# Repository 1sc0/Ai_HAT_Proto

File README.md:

## Ai\_HAT\_Proto

PCB design files (EAGLE) for a Raspberry Pi A+/B+/2/3 HAT with a
perma/proto-board section for soldering components. Features 3-Pin and 4-Pin JST
connectors.

## Description

Visit our online shop at:

   * https://acrobotic.com/

Designed by ACROBOTIC Industries.  Please consider buying products from us to 
help fund future Open-Source projects like this! We’ll always put our best 
effort in every project, and release all our design files and code for you to 
use. 

## License

Released under the Creative Commons Attribution, Share-Alike license. Please 
check LICENSE.txt for more information. All text above must be included in any 
redistribution.

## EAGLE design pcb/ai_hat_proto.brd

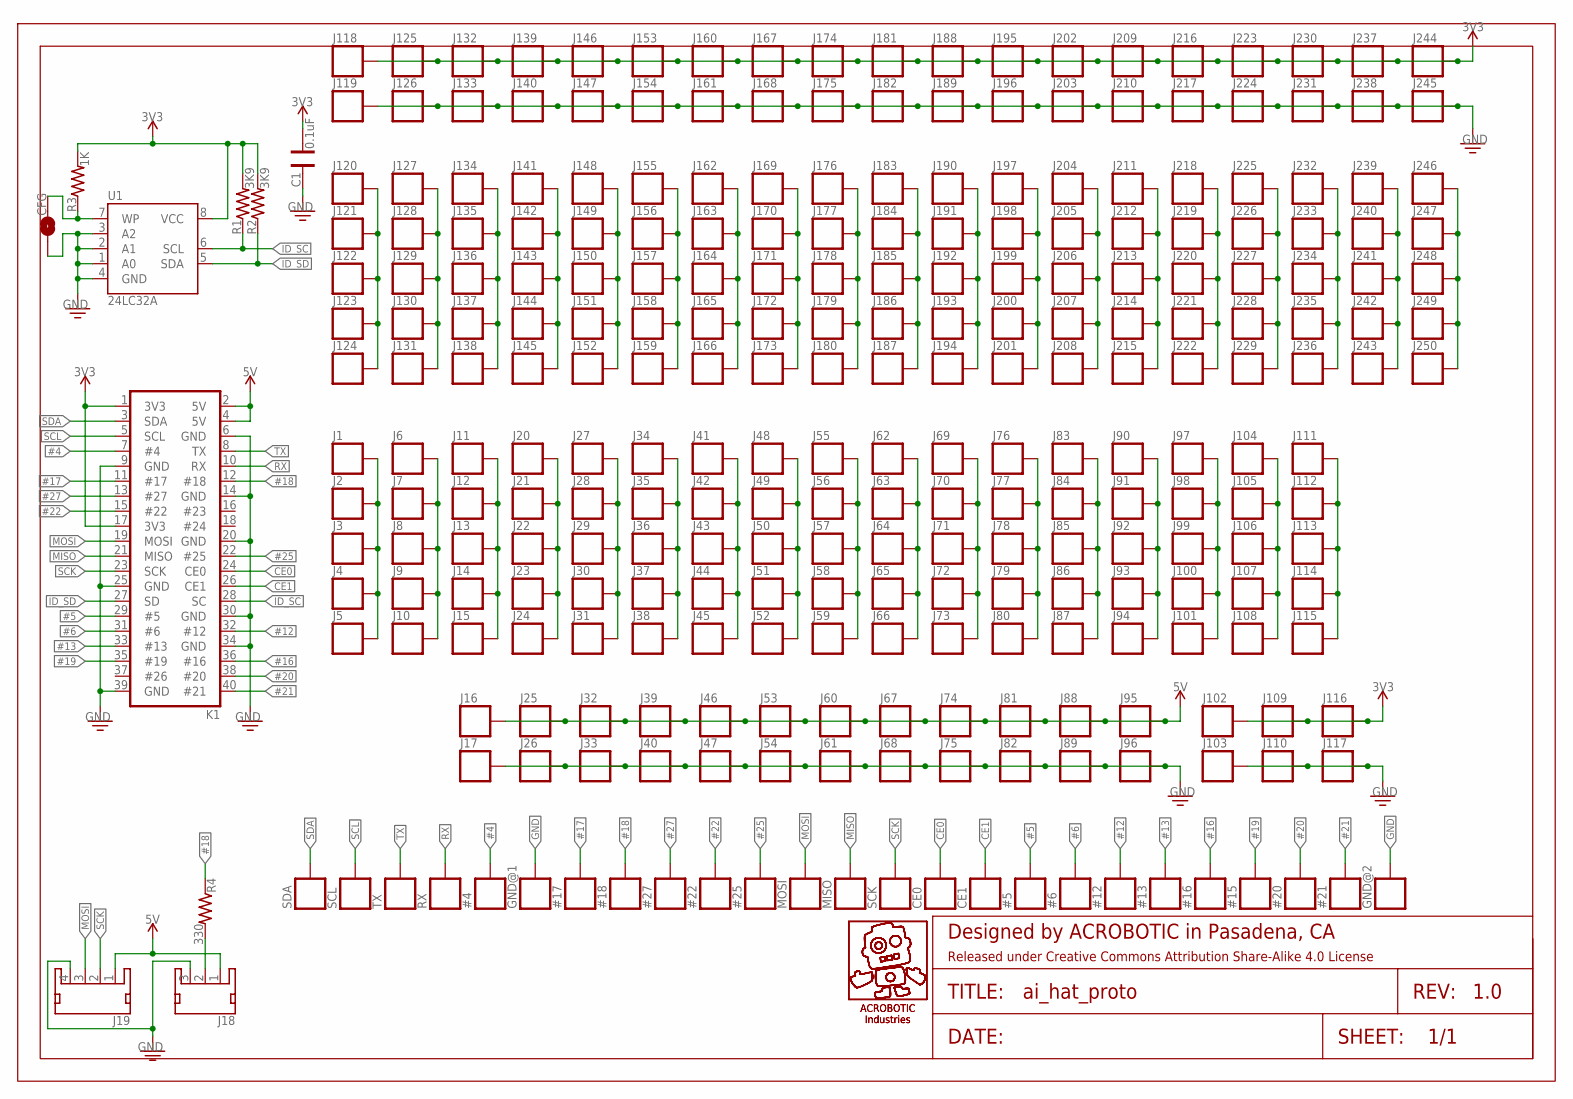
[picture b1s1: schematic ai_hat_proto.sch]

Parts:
#4, #5, #6, #12, #13, #15, #16, #17, #18, #20, #21, #22, #25, #27: 1X01-SM
C1: 0.1uF; CAP-0603
CE0, CE1: 1X01-SM
CFG: 1X02-SJ-NO
FRAME1: FRAME-LETTER; CREATIVE-COMMONS
GND@1, GND@2: 1X01-SM
J1, J2, J3, J4, J5, J6, J7, J8, J9, J10, J11, J12, J13, J14, J15, J16, J17, J20, J21, J22, J23, J24, J25, J26, J27, J28, J29, J30, J31, J32, J33, J34, J35, J36, J37, J38, J39, J40, J41, J42, J43, J44, J45, J46, J47, J48, J49, J50, J51, J52, J53, J54, J55, J56, J57, J58, J59, J60, J61, J62, J63, J64, J65, J66, J67, J68, J69, J70, J71, J72, J73, J74, J75, J76, J77, J78, J79, J80, J81, J82, J83, J84, J85, J86, J87, J88, J89, J90, J91, J92, J93, J94, J95, J96, J97, J98, J99, J100, J101, J102, J103, J104, J105, J106, J107, J108, J109, J110, J111, J112, J113, J114, J115, J116, J117, J118, J119, J120, J121, J122, J123, J124, J125, J126, J127, J128, J129, J130, J131, J132, J133, J134, J135, J136, J137, J138, J139, J140, J141, J142, J143, J144, J145, J146, J147, J148, J149, J150, J151, J152, J153, J154, J155, J156, J157, J158, J159, J160, J161, J162, J163, J164, J165, J166, J167, J168, J169, J170, J171, J172, J173, J174, J175, J176, J177, J178, J179, J180, J181, J182, J183, J184, J185, J186, J187, J188, J189, J190, J191, J192, J193, J194, J195, J196, J197, J198, J199, J200, J201, J202, J203, J204, J205, J206, J207, J208, J209, J210, J211, J212, J213, J214, J215, J216, J217, J218, J219, J220, J221, J222, J223, J224, J225, J226, J227, J228, J229, J230, J231, J232, J233, J234, J235, J236, J237, J238, J239, J240, J241, J242, J243, J244, J245, J246, J247, J248, J249, J250: 1X01-SM
J18: JST-3P-MALE; JST-3P-SMD
J19: JST-4P-MALE; JST-4P-SMD
K1: 2X20-RPI
MISO: 1X01-SM
MOSI: 1X01-SM
R1, R2: 3K9; RES-0603; TOLERANCE 5%
R3: 1K; RES-0603; TOLERANCE 5%
R4: 330; RES-0603
RX: 1X01-SM
SCK: 1X01-SM
SCL: 1X01-SM
SDA: 1X01-SM
TX: 1X01-SM
U1: 24LC32A; SO08-EIAJ
U$9, U$10: AI-LOGOXS; AI-LOGO-XS

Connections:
2: J18.2, R4.2
3V3: C1.1, J102.1, J109.1, J116.1, J118.1, J125.1, J132.1, J139.1, J146.1, J153.1, J160.1, J167.1, J174.1, J181.1, J188.1, J195.1, J202.1, J209.1, J216.1, J223.1, J230.1, J237.1, J244.1, K1.1 (3V3), K1.17 (3V3), R1.2, R2.2, R3.2, U1.8 (VCC)
5V: J16.1, J18.1, J19.1, J25.1, J32.1, J39.1, J46.1, J53.1, J60.1, J67.1, J74.1, J81.1, J88.1, J95.1, K1.2 (5V), K1.4 (5V)
#4: #4.1, K1.7 (#4)
#5: #5.1, K1.29 (#5)
#6: #6.1, K1.31 (#6)
#12: #12.1, K1.32 (#12)
#13: #13.1, K1.33 (#13)
#16: #16.1, K1.36 (#16)
#17: #17.1, K1.11 (#17)
#18: #18.1, K1.12 (#18), R4.1
#19: #15.1, K1.35 (#19)
#20: #20.1, K1.38 (#20)
#21: #21.1, K1.40 (#21)
#22: #22.1, K1.15 (#22)
#25: #25.1, K1.22 (#25)
#27: #27.1, K1.13 (#27)
CE0: CE0.1, K1.24 (CE0)
CE1: CE1.1, K1.26 (CE1)
GND: C1.2, CFG.1, GND@1.1, GND@2.1, J17.1, J18.3, J19.4, J26.1, J33.1, J40.1, J47.1, J54.1, J61.1, J68.1, J75.1, J82.1, J89.1, J96.1, J103.1, J110.1, J117.1, J119.1, J126.1, J133.1, J140.1, J147.1, J154.1, J161.1, J168.1, J175.1, J182.1, J189.1, J196.1, J203.1, J210.1, J217.1, J224.1, J231.1, J238.1, J245.1, K1.6 (GND), K1.9 (GND), K1.14 (GND), K1.20 (GND), K1.25 (GND), K1.30 (GND), K1.34 (GND), K1.39 (GND), U1.1 (A0), U1.2 (A1), U1.3 (A2), U1.4 (GND)
ID_SC: K1.28 (SC), R1.1, U1.6 (SCL)
ID_SD: K1.27 (SD), R2.1, U1.5 (SDA)
MISO: K1.21 (MISO), MISO.1
MOSI: J19.3, K1.19 (MOSI), MOSI.1
unnamed: J1.1, J2.1, J3.1, J4.1, J5.1
unnamed: J6.1, J7.1, J8.1, J9.1, J10.1
unnamed: CFG.2, R3.1, U1.7 (WP)
unnamed: J11.1, J12.1, J13.1, J14.1, J15.1
unnamed: J20.1, J21.1, J22.1, J23.1, J24.1
unnamed: J27.1, J28.1, J29.1, J30.1, J31.1
unnamed: J34.1, J35.1, J36.1, J37.1, J38.1
unnamed: J41.1, J42.1, J43.1, J44.1, J45.1
unnamed: J48.1, J49.1, J50.1, J51.1, J52.1
unnamed: J55.1, J56.1, J57.1, J58.1, J59.1
unnamed: J62.1, J63.1, J64.1, J65.1, J66.1
unnamed: J69.1, J70.1, J71.1, J72.1, J73.1
unnamed: J76.1, J77.1, J78.1, J79.1, J80.1
unnamed: J83.1, J84.1, J85.1, J86.1, J87.1
unnamed: J90.1, J91.1, J92.1, J93.1, J94.1
unnamed: J97.1, J98.1, J99.1, J100.1, J101.1
unnamed: J104.1, J105.1, J106.1, J107.1, J108.1
unnamed: J111.1, J112.1, J113.1, J114.1, J115.1
unnamed: J120.1, J121.1, J122.1, J123.1, J124.1
unnamed: J127.1, J128.1, J129.1, J130.1, J131.1
unnamed: J134.1, J135.1, J136.1, J137.1, J138.1
unnamed: J141.1, J142.1, J143.1, J144.1, J145.1
unnamed: J148.1, J149.1, J150.1, J151.1, J152.1
unnamed: J155.1, J156.1, J157.1, J158.1, J159.1
unnamed: J162.1, J163.1, J164.1, J165.1, J166.1
unnamed: J169.1, J170.1, J171.1, J172.1, J173.1
unnamed: J176.1, J177.1, J178.1, J179.1, J180.1
unnamed: J183.1, J184.1, J185.1, J186.1, J187.1
unnamed: J190.1, J191.1, J192.1, J193.1, J194.1
unnamed: J197.1, J198.1, J199.1, J200.1, J201.1
unnamed: J204.1, J205.1, J206.1, J207.1, J208.1
unnamed: J211.1, J212.1, J213.1, J214.1, J215.1
unnamed: J218.1, J219.1, J220.1, J221.1, J222.1
unnamed: J225.1, J226.1, J227.1, J228.1, J229.1
unnamed: J232.1, J233.1, J234.1, J235.1, J236.1
unnamed: J239.1, J240.1, J241.1, J242.1, J243.1
unnamed: J246.1, J247.1, J248.1, J249.1, J250.1
RX: K1.10 (RX), RX.1
SCK: J19.2, K1.23 (SCK), SCK.1
SCL: K1.5 (SCL), SCL.1
SDA: K1.3 (SDA), SDA.1
TX: K1.8 (TX), TX.1

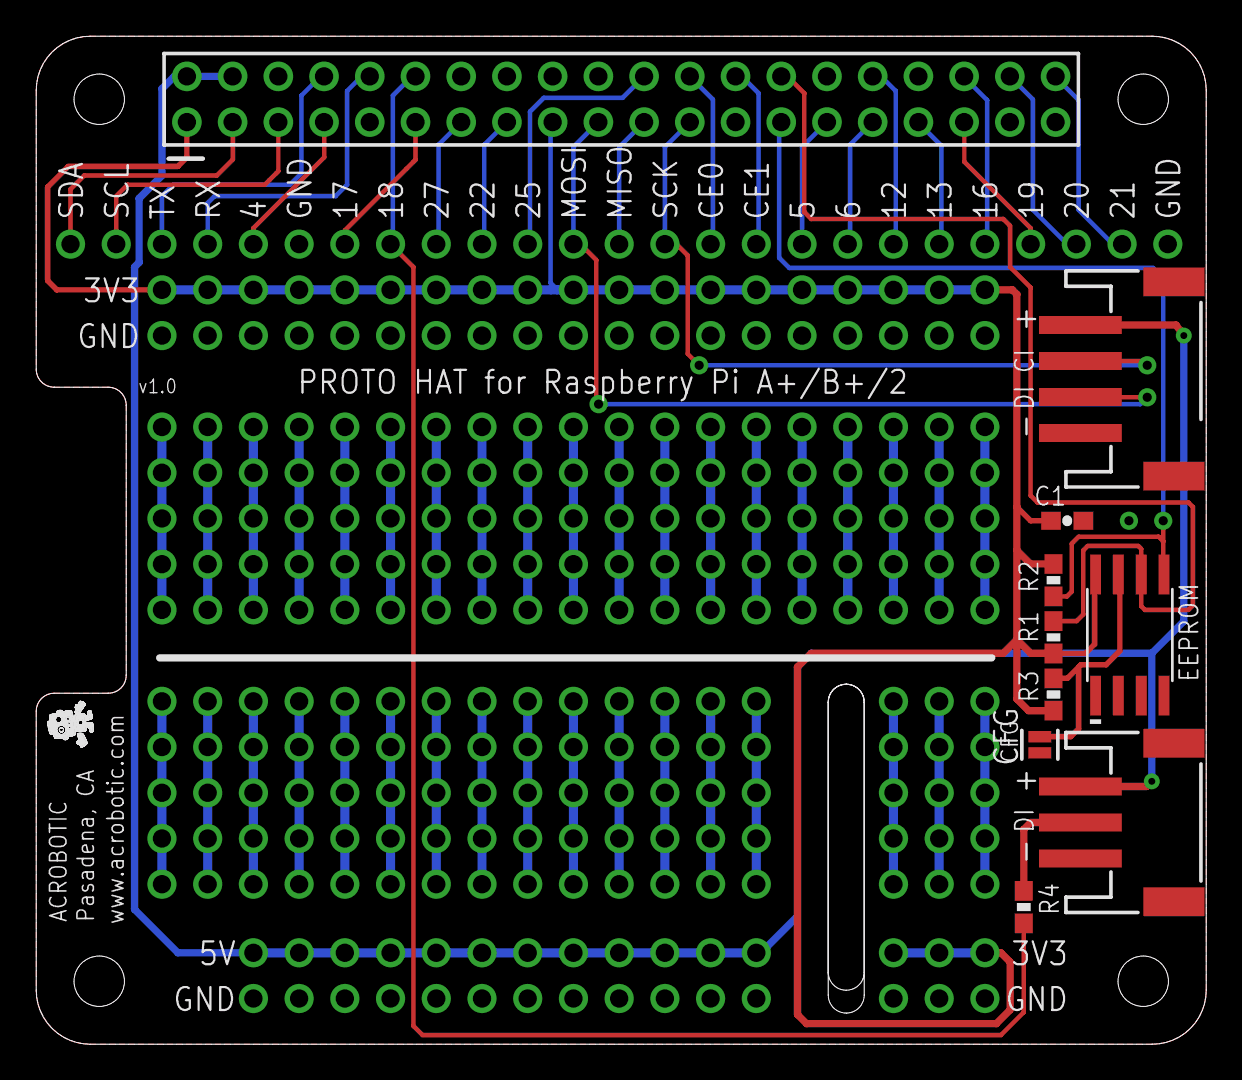
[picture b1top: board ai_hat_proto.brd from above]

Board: 2 copper layers, 65.0 x 56.0 mm, 286 parts (1 on the bottom side), 66 nets.

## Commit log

2015-04-25 updating
2015-05-01 changed resistor value

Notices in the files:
parts and their libraries:
Ai_Miscellany: Attribution Share-Alike 4.0 License
Ai_Miscellany: https://creativecommons.org/licenses/by-sa/4.0
Ai_Miscellany: Released under Creative Commons Attribution Share-Alike 4.0 License
